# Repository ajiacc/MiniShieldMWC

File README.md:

# MiniShieldMWC
<p>A pro mini shield for MWC
<p>With nRF24L01 mini board mounted

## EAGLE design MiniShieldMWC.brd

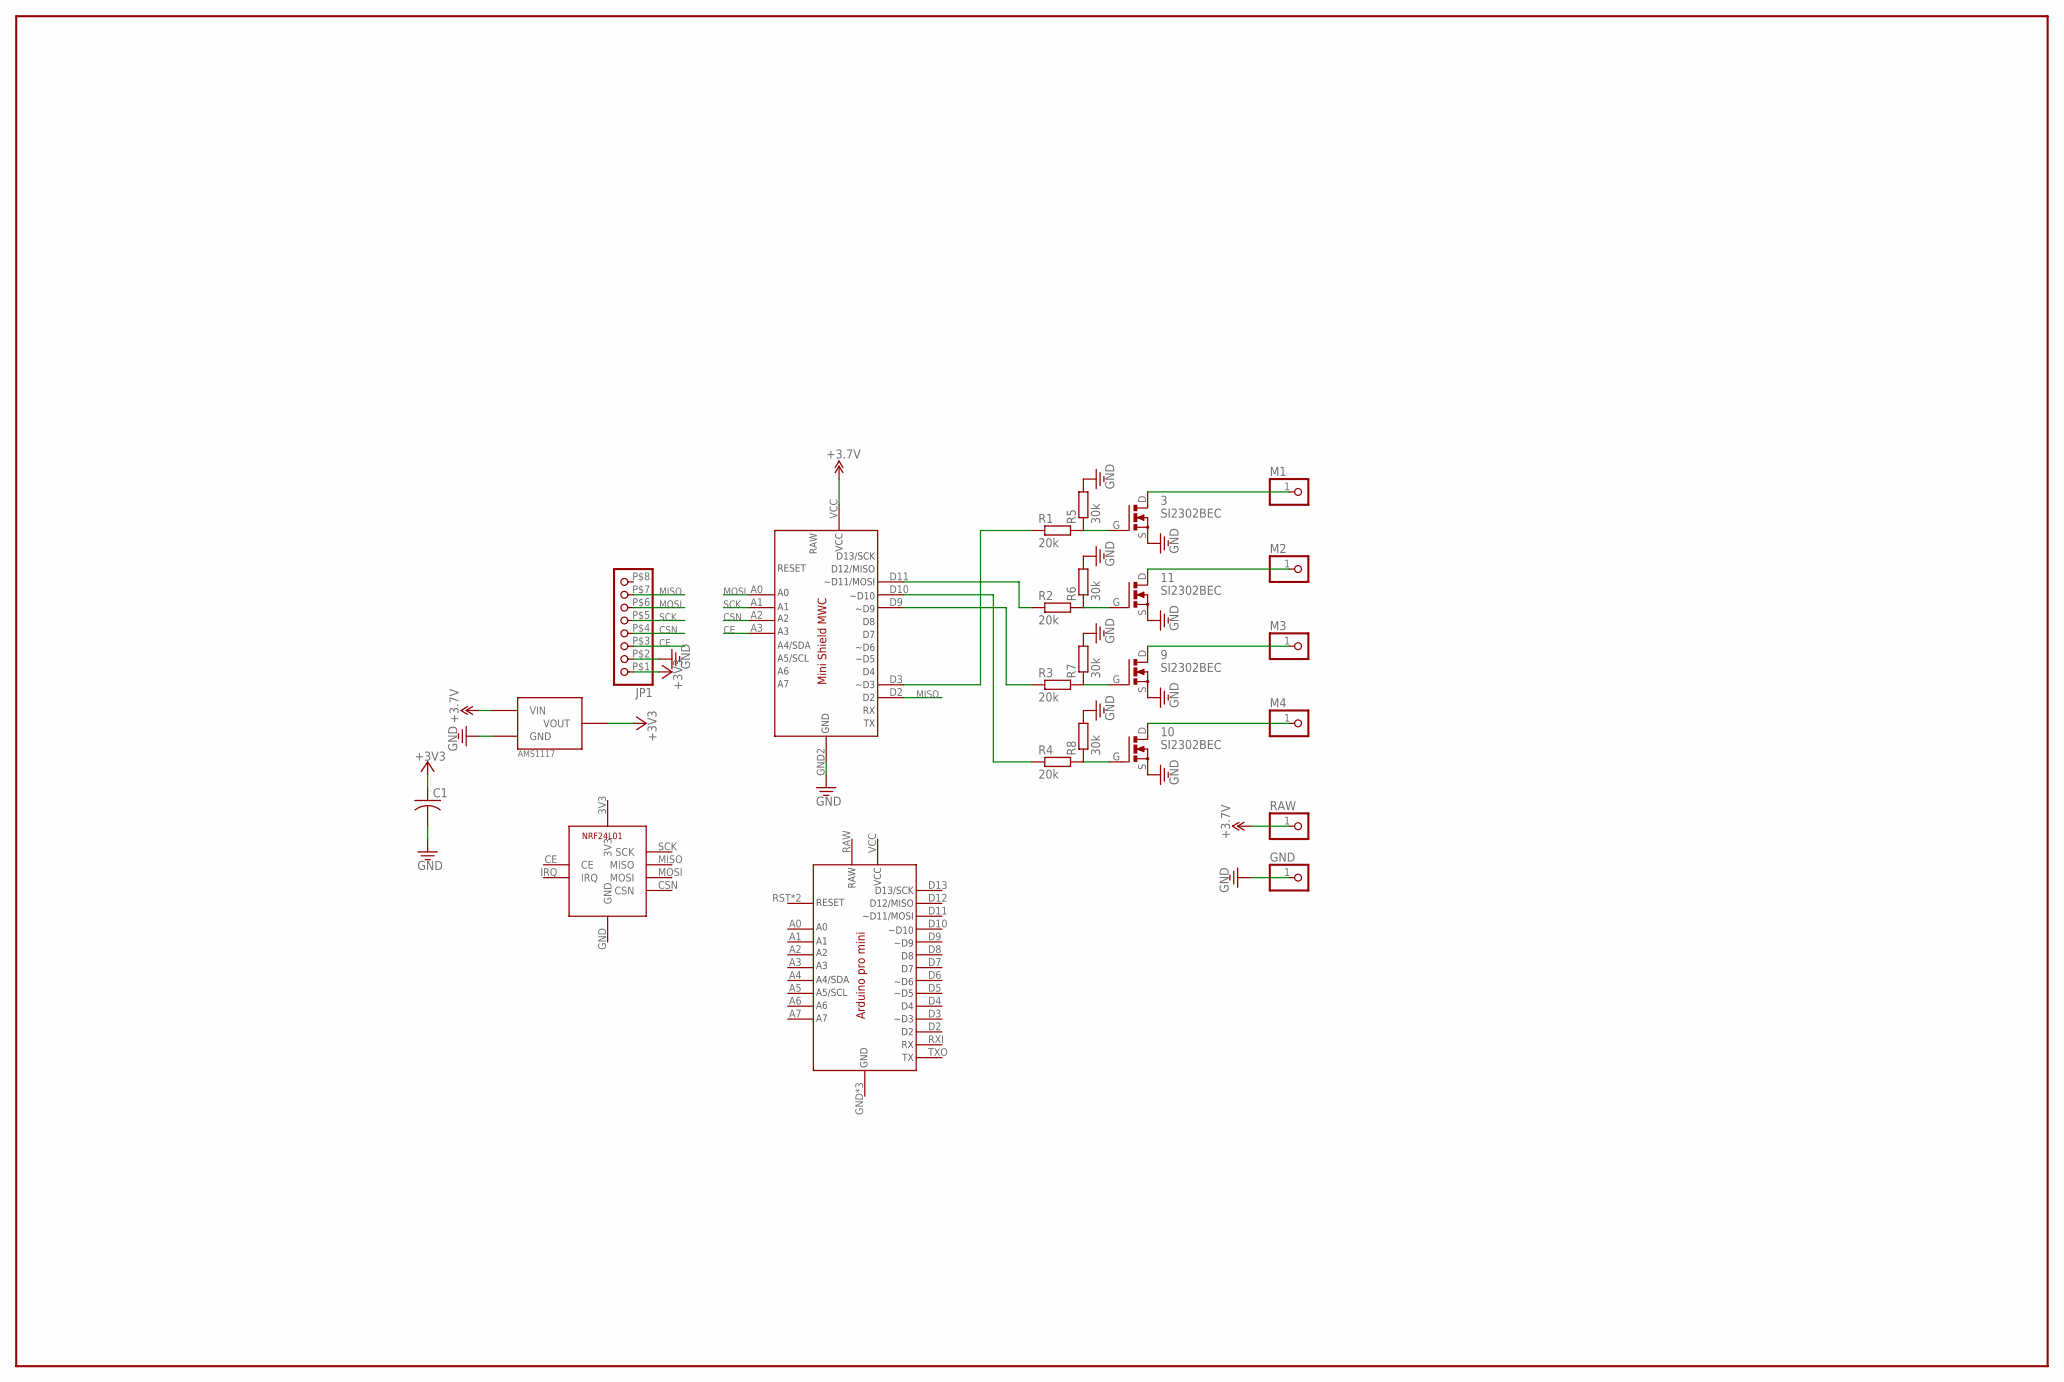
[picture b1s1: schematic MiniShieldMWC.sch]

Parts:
3, 9, 10, 11: SI2302BEC; SOT23-BEC
C1: C-USC0805; C0805
GND: PINHD-1X1; 1X01
JP1: PINHD-1X8MINI; PINHD_MINI_X8
M1, M2, M3, M4: PINHD-1X1; 1X01
R1, R2, R3, R4: 20k; M0805
R5, R6, R7, R8: 30k; M0805
RAW: PINHD-1X1; 1X01
U$1: ARDUINO_PRO_MINI
U$2: NRF24L01MINI; NRF24L01_MINI
U$3: AMS1117
U$4: MINI_SHIELD_MWC

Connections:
3V3: U$2.3V3
+3V3: C1.1, JP1.P$1 (1), U$3.VOUT, U$3.VOUT1 (VOUT)
CE: JP1.P$3 (3), U$4.A3
CSN: JP1.P$4 (4), U$4.A2
GND: 3.S, 9.S, 10.S, 11.S, C1.2, GND.1, JP1.P$2 (2), R5.2, R6.2, R7.2, R8.2, U$1.GND, U$1.GND1 (GND), U$1.GND2 (GND), U$2.GND, U$3.GND, U$4.GND2 (GND)
MISO: JP1.P$7 (7), U$4.D2
MOSI: JP1.P$6 (6), U$4.A0
unnamed: 3.G, R1.2, R5.1
unnamed: 11.G, R2.2, R6.1
unnamed: 9.G, R3.2, R7.1
unnamed: 10.G, R4.2, R8.1
unnamed: R1.1, U$4.D3 (~D3)
unnamed: R2.1, U$4.D11 (~D11)
unnamed: R3.1, U$4.D9 (~D9)
unnamed: R4.1, U$4.D10 (~D10)
unnamed: 10.D, M4.1
unnamed: 9.D, M3.1
unnamed: 11.D, M2.1
unnamed: 3.D, M1.1
unnamed: RAW.1, U$3.VIN, U$4.VCC
RAW: U$1.RAW
SCK: JP1.P$5 (5), U$4.A1
VCC: U$1.VCC

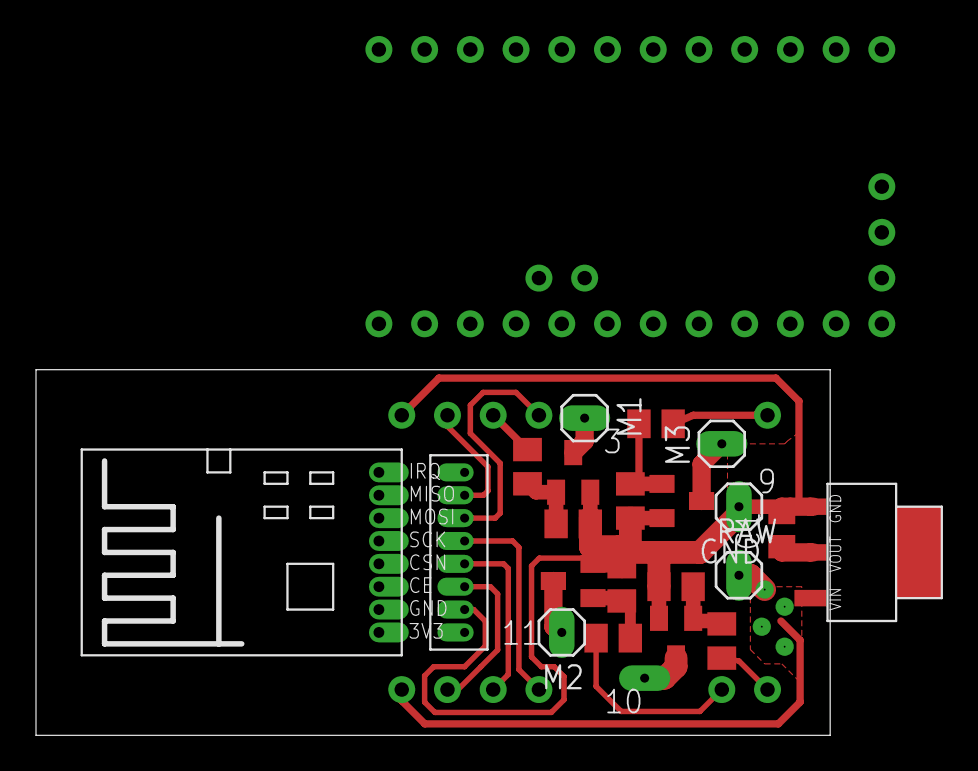
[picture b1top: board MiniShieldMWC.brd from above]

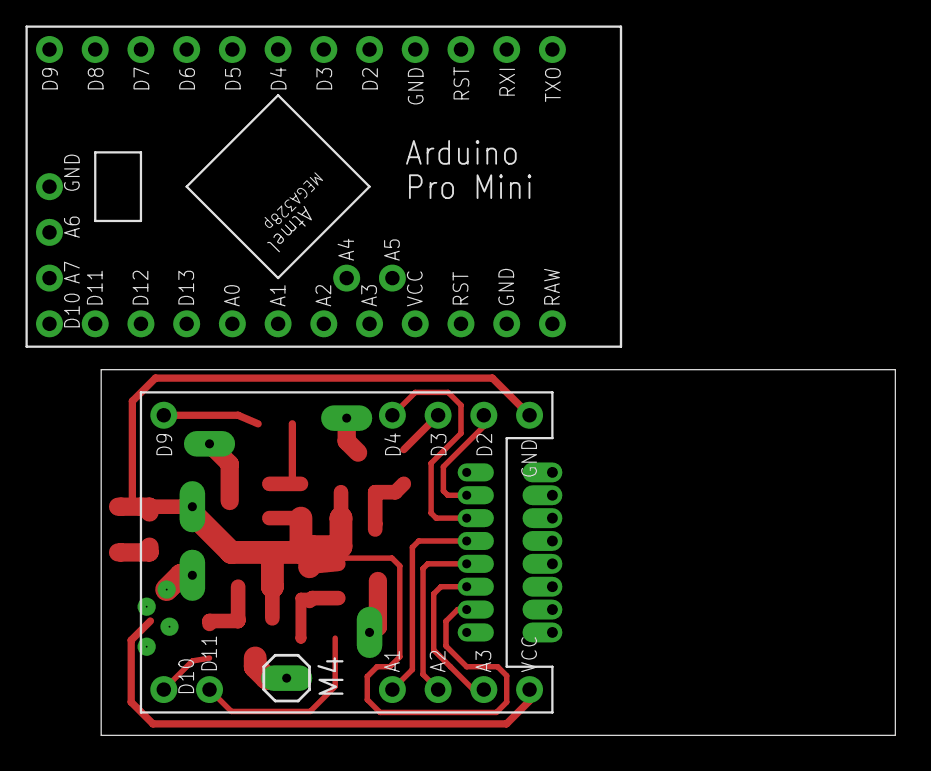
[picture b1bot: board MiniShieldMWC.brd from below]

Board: 2 copper layers, 44.1 x 20.3 mm, 24 parts (2 on the bottom side), 20 nets.

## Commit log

2016-03-08 1.1.1
2016-03-09 1.1.2
